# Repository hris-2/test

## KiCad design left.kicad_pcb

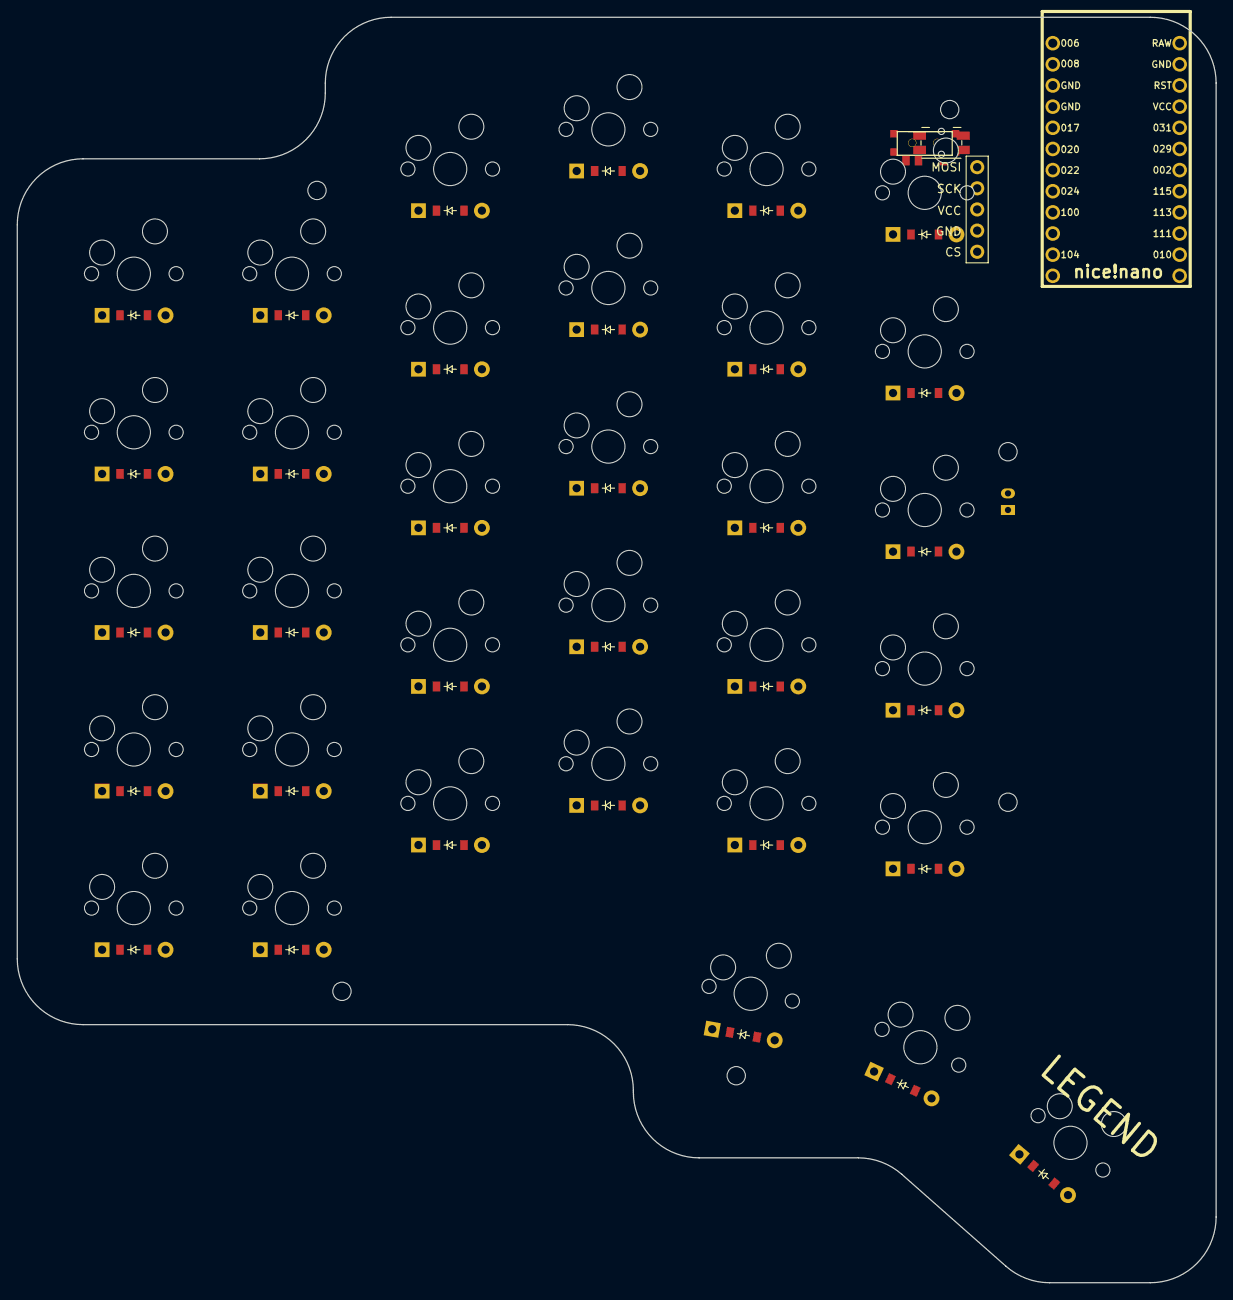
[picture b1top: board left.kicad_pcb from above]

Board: 2 copper layers, 144.0 x 152.0 mm, 77 parts (0 on the bottom side), 50 nets, no tracks yet.

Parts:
B1: Panasonic_EVQPUL_EVQPUC
D1, D2, D3, D4, D5, D6, D7, D8, D9, D10, D11, D12, D13, D14, D15, D16, D17, D18, D19, D20, D21, D22, D23, D24, D25, D26, D27, D28, D29, D30, D31, D32, D33: ComboDiode
DISP1: display_nice_view
JST1: JST_PH_S2B-PH-K_02x2.00mm_Angled
MCU1: nice_nano
MH1, MH2, MH3, MH4, MH5, MH6: mounting_hole_npth
S1, S2, S3, S4, S5, S6, S7, S8, S9, S10, S11, S12, S13, S14, S15, S16, S17, S18, S19, S20, S21, S22, S23, S24, S25, S26, S27, S28, S29, S30, S31, S32, S33: MX
T1: SPDT_C128955

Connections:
GND: B1.1, DISP1.4, JST1.2, MCU1.3, MCU1.4, MCU1.23
RAW: MCU1.24, T1.2
RST: B1.2, MCU1.22
VCC: DISP1.3, MCU1.21
col_1: MCU1.1, S26.1, S27.1, S28.1, S29.1, S30.1, S33.1
col_2: MCU1.2, S21.1, S22.1, S23.1, S24.1, S25.1, S32.1
col_3: MCU1.5, S16.1, S17.1, S18.1, S19.1, S20.1, S31.1
col_4: MCU1.6, S11.1, S12.1, S13.1, S14.1, S15.1
col_5: MCU1.7, S6.1, S7.1, S8.1, S9.1, S10.1
col_6: MCU1.8, S1.1, S2.1, S3.1, S4.1, S5.1
in_default: D31.2, S31.2
index_bottom: D22.2, S22.2
index_control: D21.2, S21.2
index_home: D23.2, S23.2
index_num: D25.2, S25.2
index_top: D24.2, S24.2
inner_bottom: D27.2, S27.2
inner_control: D26.2, S26.2
inner_home: D28.2, S28.2
inner_num: D30.2, S30.2
inner_top: D29.2, S29.2
mid_default: D32.2, S32.2
middle_bottom: D17.2, S17.2
middle_control: D16.2, S16.2
middle_home: D18.2, S18.2
middle_num: D20.2, S20.2
middle_top: D19.2, S19.2
out_default: D33.2, S33.2
outer_bottom: D2.2, S2.2
outer_control: D1.2, S1.2
outer_home: D3.2, S3.2
outer_num: D5.2, S5.2
outer_top: D4.2, S4.2
pinky_bottom: D7.2, S7.2
pinky_control: D6.2, S6.2
pinky_home: D8.2, S8.2
pinky_num: D10.2, S10.2
pinky_top: D9.2, S9.2
pos: JST1.1, T1.1
ring_bottom: D12.2, S12.2
ring_control: D11.2, S11.2
ring_home: D13.2, S13.2
ring_num: D15.2, S15.2
ring_top: D14.2, S14.2
row_1: D5.1, D10.1, D15.1, D20.1, D25.1, D30.1, MCU1.9
row_2: D4.1, D9.1, D14.1, D19.1, D24.1, D29.1, MCU1.10
row_3: D3.1, D8.1, D13.1, D18.1, D23.1, D28.1, MCU1.11
row_4: D2.1, D7.1, D12.1, D17.1, D22.1, D27.1, MCU1.12
row_5: D1.1, D6.1, D11.1, D16.1, D21.1, D26.1, MCU1.13
thumb_1: D31.1, D32.1, D33.1, MCU1.15
